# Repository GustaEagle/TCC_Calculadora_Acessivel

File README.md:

# Calculadora científica acessível (TCC)

Calculadora científica com foco em **acessibilidade** (feedback por voz e operação sem depender só da tela), executada em **Raspberry Pi 4B** com teclado físico, **UPS HAT**, painel **LCD 4,3" Waveshare** e suporte a **monitor HDMI**.

**Equipe:** Gustavo, João, Yuri  

**Repositório:** [github.com/GustaEagle/TCC_Calculadora_Acessivel](https://github.com/GustaEagle/TCC_Calculadora_Acessivel)

---

## Documentação principal

A pasta [`docs/`](docs/README.md) está organizada **por contexto** — comece pelo índice, ou vá direto ao documento:

| Documento | Descrição |
| --------- | --------- |
| [docs/README.md](docs/README.md) | **Índice da documentação** — o que existe e em que pasta |
| [docs/produto/PRD.md](docs/produto/PRD.md) | Requisitos de produto, escopo e arquitetura em alto nível (**normativo**) |
| [docs/guias/teclado-matriz.md](docs/guias/teclado-matriz.md) | **Teclado físico (matriz 6×7)**: as 38 teclas, funções com Ctrl/Shift, GPIO e diagnóstico |
| [docs/guias/comandos-teclado.md](docs/guias/comandos-teclado.md) | Comandos no teclado de PC: Ctrl/Shift, histórico, última resposta |
| [docs/guias/build-img-linux.md](docs/guias/build-img-linux.md) | Arranque em modo kiosk no Raspberry Pi 4B |
| [docs/desenvolvimento/Sprints.md](docs/desenvolvimento/Sprints.md) | Backlog por sprint e estado das tasks |
| [docs/desenvolvimento/GITHUB_WORKFLOW.md](docs/desenvolvimento/GITHUB_WORKFLOW.md) | Fluxo Git/GitHub da equipe |
| [docs/desenvolvimento/REPO_STRUCTURE.md](docs/desenvolvimento/REPO_STRUCTURE.md) | Mapa de pastas (software, hardware, system) |
| [docs/desenvolvimento/CONTEXT.md](docs/desenvolvimento/CONTEXT.md) | Memória curta entre sessões |
| [cronograma/cronograma.md](cronograma/cronograma.md) | Linha do tempo académica |

---

## Executar

```bash
python -m pip install -r software/requirements.txt
python software/app.py
```

`software/app.py` deteta a saída de vídeo ativa e abre **um** front (PRD §7): monitor HDMI externo quando reconhecido, senão o LCD 4,3", e **modo somente áudio** quando não há vídeo utilizável.

Para desenvolvimento e demonstrações a saída pode ser forçada:

```bash
python software/app.py --force-mode hdmi   # front do monitor externo
python software/app.py --force-mode lcd    # front do painel 4,3"
python software/app.py --force-mode audio  # somente voz, sem janela
```

**Histórico:** abre por **Ctrl + Ans** (no PC, a tecla `a` faz o papel do `Ans` da matriz 6x7). Não há botão de histórico — a entrada é sempre pelo teclado.

Lista completa dos atalhos: [docs/guias/teclado-matriz.md](docs/guias/teclado-matriz.md) (teclado do produto) e [docs/guias/comandos-teclado.md](docs/guias/comandos-teclado.md) (teclado de PC).

Testes: `make check` (ou `python -m unittest discover -s software/tests -t .`).

---

## Estrutura do repositório (resumo)

- **`software/`** — Motor de cálculo, UI (LCD / HDMI / partilhada), acessibilidade (áudio/TTS), plataforma (GPIO, integração), ponto de entrada `app.py`
- **`hardware/`** — PCB (KiCad), snapshots de export para marcos
- **`system/`** — Imagem SO, arranque e scripts (evolução conforme o PRD)
- **`docs/`** — Documentação por contexto: `produto/` (PRD), `guias/` (uso e montagem), `desenvolvimento/` (processo), `testes/`, mais referência de hardware (`raspberry-pi-4b/`, `waveshare/`, `keyboard-layout/`, `cad/`)
- **`cronograma/`** — Cronograma em Markdown, HTML interativo e export bruto
- **`prompts/`** — Prompts de sessão (bootstrap, fecho, agentes)

---

## Contribuir

1. Clonar o repositório e entrar na pasta do projeto  
2. Ler [docs/desenvolvimento/GITHUB_WORKFLOW.md](docs/desenvolvimento/GITHUB_WORKFLOW.md) e, no início de cada sessão, seguir [prompts/bootstrap.txt](prompts/bootstrap.txt)  
3. Trabalhar em branch a partir de `main` atualizada; mensagens de commit em **inglês** (ver [.github/COMMIT_GUIDELINES.md](.github/COMMIT_GUIDELINES.md))

---

## Estado do projeto

O código de aplicação ainda está em estruturação; o PRD e a documentação de apoio são a referência normativa. Consulte [docs/desenvolvimento/Sprints.md](docs/desenvolvimento/Sprints.md) para a sprint corrente e próximos entregáveis.

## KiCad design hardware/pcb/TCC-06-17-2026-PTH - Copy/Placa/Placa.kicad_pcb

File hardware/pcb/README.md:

# PCB — KiCad

Coloque aqui o **projeto principal** (ex.: `tcc-calculadora/` com `.kicad_pro`).

## Snapshots (marcos)

Exportações conscientes (não substituem o Git do projeto):

```
snapshots/
  2026-05-01-pre-banca/
  2026-06-10-entrega/
```

Cada pasta pode conter: Gerber ZIP, PDF do esquemático, lista de materiais, notas de revisão.

## O que não versionar

A pasta **`.history/`** gerada pelo KiCad fica fora do Git (ver `.gitignore` na raiz).

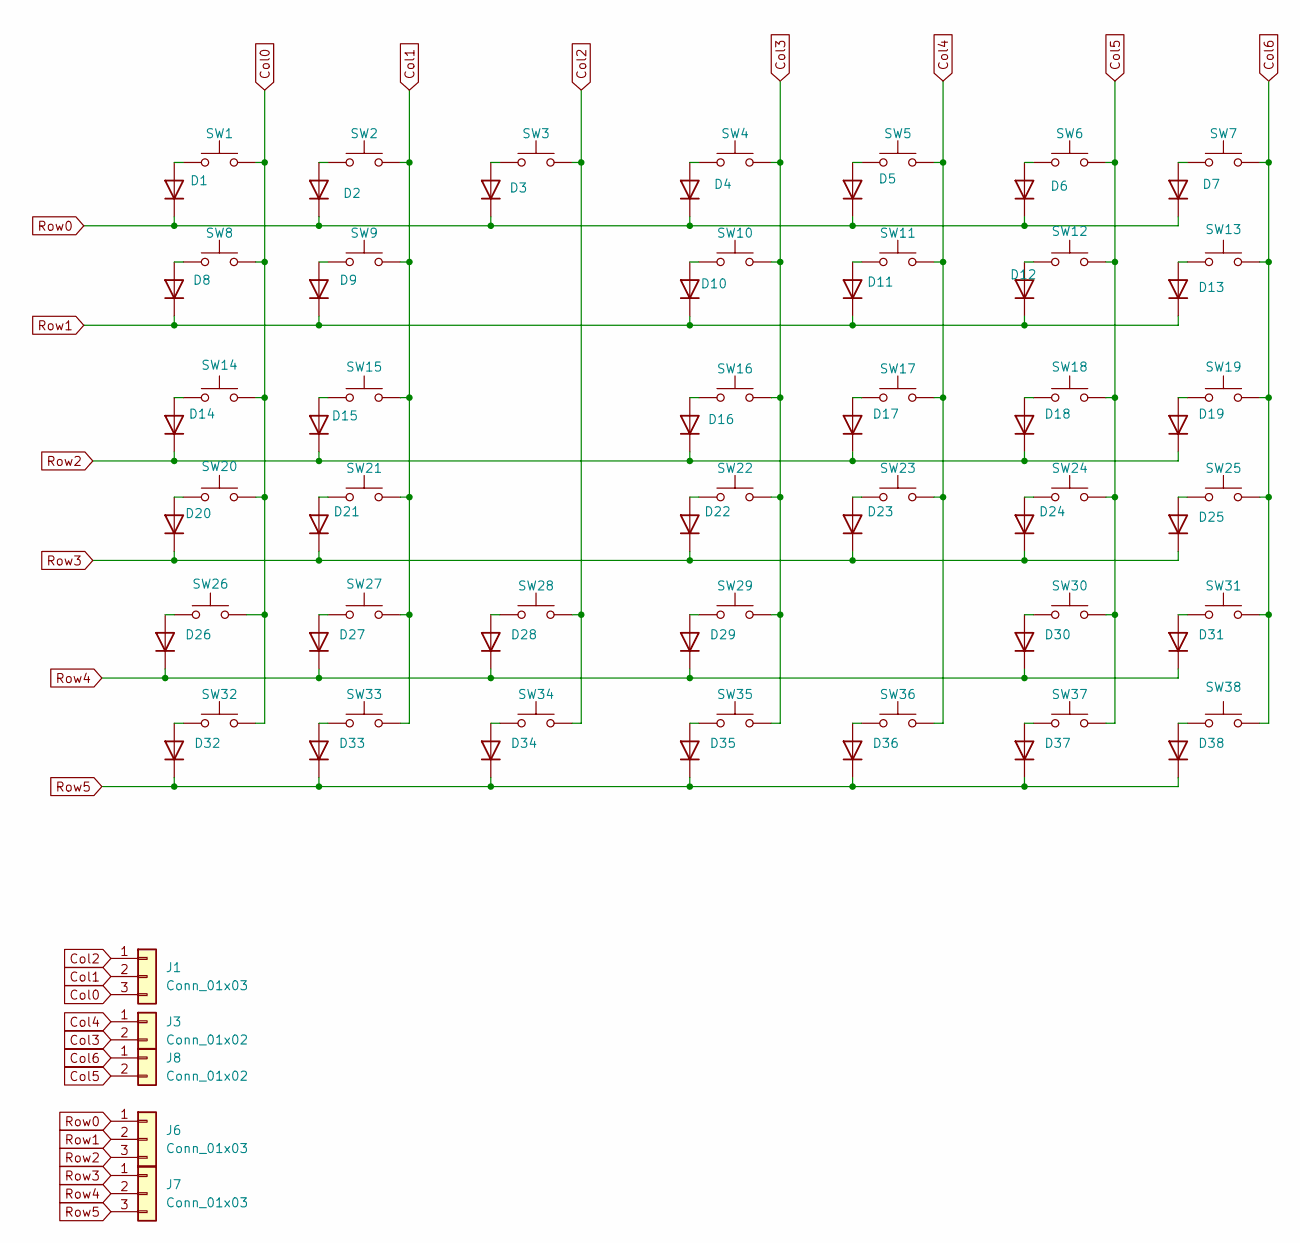
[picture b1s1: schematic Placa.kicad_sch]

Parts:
D1, D2, D3, D4, D5, D6, D7, D8, D9, D10, D11, D12, D13, D14, D15, D16, D17, D18, D19, D20, D21, D22, D23, D24, D25, D26, D27, D28, D29, D30, D31, D32, D33, D34, D35, D36, D37, D38: 1N4148; D_DO-35_SOD27_P7.62mm_Horizontal
J1, J6, J7: Conn_01x03; JST_XH_B3B-XH-A_1x03_P2.50mm_Vertical
J3, J8: Conn_01x02; JST_XH_B2B-XH-A_1x02_P2.50mm_Vertical
SW1, SW2, SW3, SW4, SW5, SW6, SW7, SW8, SW9, SW10, SW11, SW12, SW13, SW14, SW15, SW16, SW17, SW18, SW19, SW20, SW21, SW22, SW23, SW24, SW25, SW26, SW27, SW28, SW29, SW30, SW31, SW32, SW33, SW34, SW35, SW36, SW37, SW38: SW_Push; Kailh_socket_MX_platemount

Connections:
Col0: J1.3, SW1.2, SW8.2, SW14.2, SW20.2, SW26.2, SW32.2
Col1: J1.2, SW2.2, SW9.2, SW15.2, SW21.2, SW27.2, SW33.2
Col2: J1.1, SW3.2, SW28.2, SW34.2
Col3: J3.2, SW4.2, SW10.2, SW16.2, SW22.2, SW29.2, SW35.2
Col4: J3.1, SW5.2, SW11.2, SW17.2, SW23.2, SW36.2
Col5: J8.2, SW6.2, SW12.2, SW18.2, SW24.2, SW30.2, SW37.2
Col6: J8.1, SW7.2, SW13.2, SW19.2, SW25.2, SW31.2, SW38.2
unnamed: D1.2 (A), SW1.1
unnamed: D2.2 (A), SW2.1
unnamed: D3.2 (A), SW3.1
unnamed: D4.2 (A), SW4.1
unnamed: D5.2 (A), SW5.1
unnamed: D6.2 (A), SW6.1
unnamed: D7.2 (A), SW7.1
unnamed: D8.2 (A), SW8.1
unnamed: D9.2 (A), SW9.1
unnamed: D10.2 (A), SW10.1
unnamed: D11.2 (A), SW11.1
unnamed: D12.2 (A), SW12.1
unnamed: D13.2 (A), SW13.1
unnamed: D14.2 (A), SW14.1
unnamed: D15.2 (A), SW15.1
unnamed: D16.2 (A), SW16.1
unnamed: D17.2 (A), SW17.1
unnamed: D18.2 (A), SW18.1
unnamed: D19.2 (A), SW19.1
unnamed: D20.2 (A), SW20.1
unnamed: D21.2 (A), SW21.1
unnamed: D22.2 (A), SW22.1
unnamed: D23.2 (A), SW23.1
unnamed: D24.2 (A), SW24.1
unnamed: D25.2 (A), SW25.1
unnamed: D26.2 (A), SW26.1
unnamed: D27.2 (A), SW27.1
unnamed: D28.2 (A), SW28.1
unnamed: D29.2 (A), SW29.1
unnamed: D30.2 (A), SW30.1
unnamed: D31.2 (A), SW31.1
unnamed: D32.2 (A), SW32.1
unnamed: D33.2 (A), SW33.1
unnamed: D34.2 (A), SW34.1
unnamed: D35.2 (A), SW35.1
unnamed: D36.2 (A), SW36.1
unnamed: D37.2 (A), SW37.1
unnamed: D38.2 (A), SW38.1
Row0: D1.1 (K), D2.1 (K), D3.1 (K), D4.1 (K), D5.1 (K), D6.1 (K), D7.1 (K), J6.1
Row1: D8.1 (K), D9.1 (K), D10.1 (K), D11.1 (K), D12.1 (K), D13.1 (K), J6.2
Row2: D14.1 (K), D15.1 (K), D16.1 (K), D17.1 (K), D18.1 (K), D19.1 (K), J6.3
Row3: D20.1 (K), D21.1 (K), D22.1 (K), D23.1 (K), D24.1 (K), D25.1 (K), J7.1
Row4: D26.1 (K), D27.1 (K), D28.1 (K), D29.1 (K), D30.1 (K), D31.1 (K), J7.2
Row5: D32.1 (K), D33.1 (K), D34.1 (K), D35.1 (K), D36.1 (K), D37.1 (K), D38.1 (K), J7.3

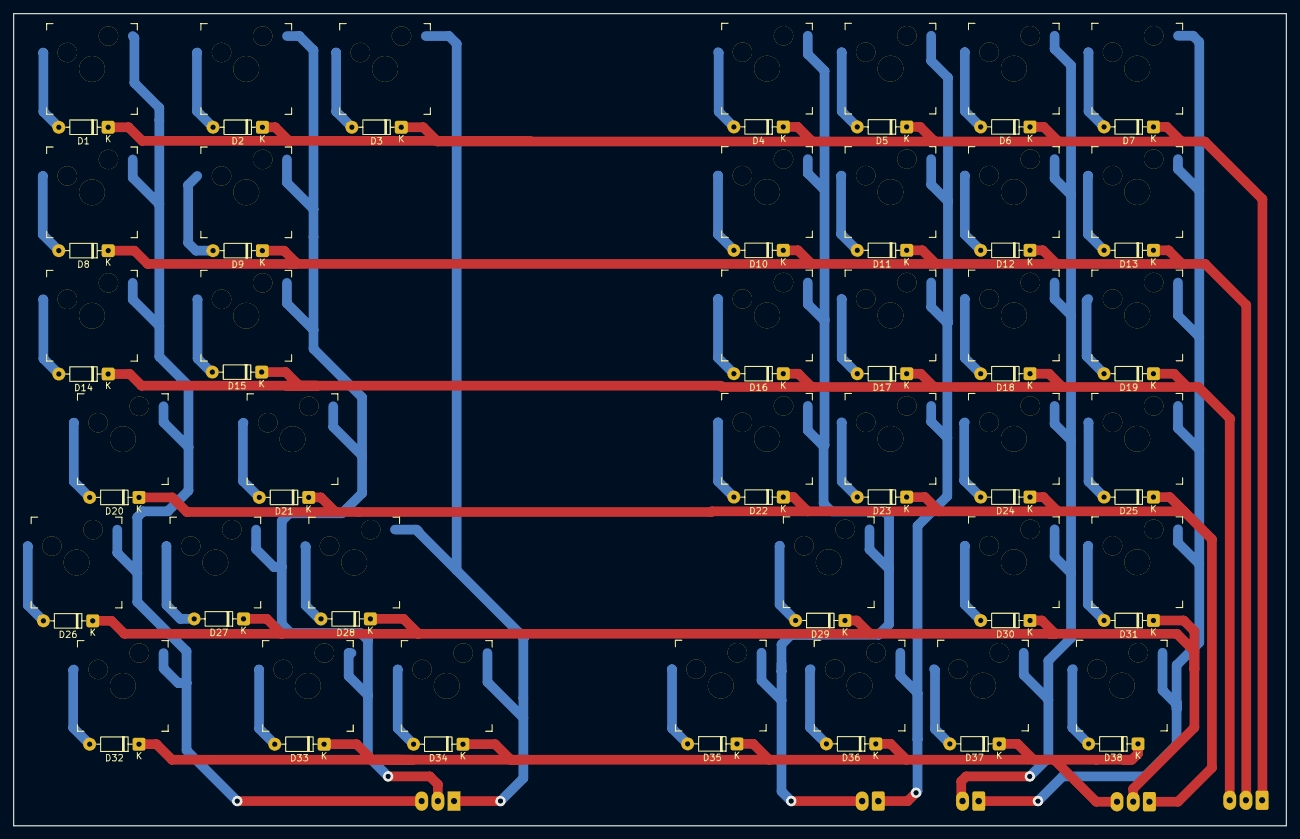
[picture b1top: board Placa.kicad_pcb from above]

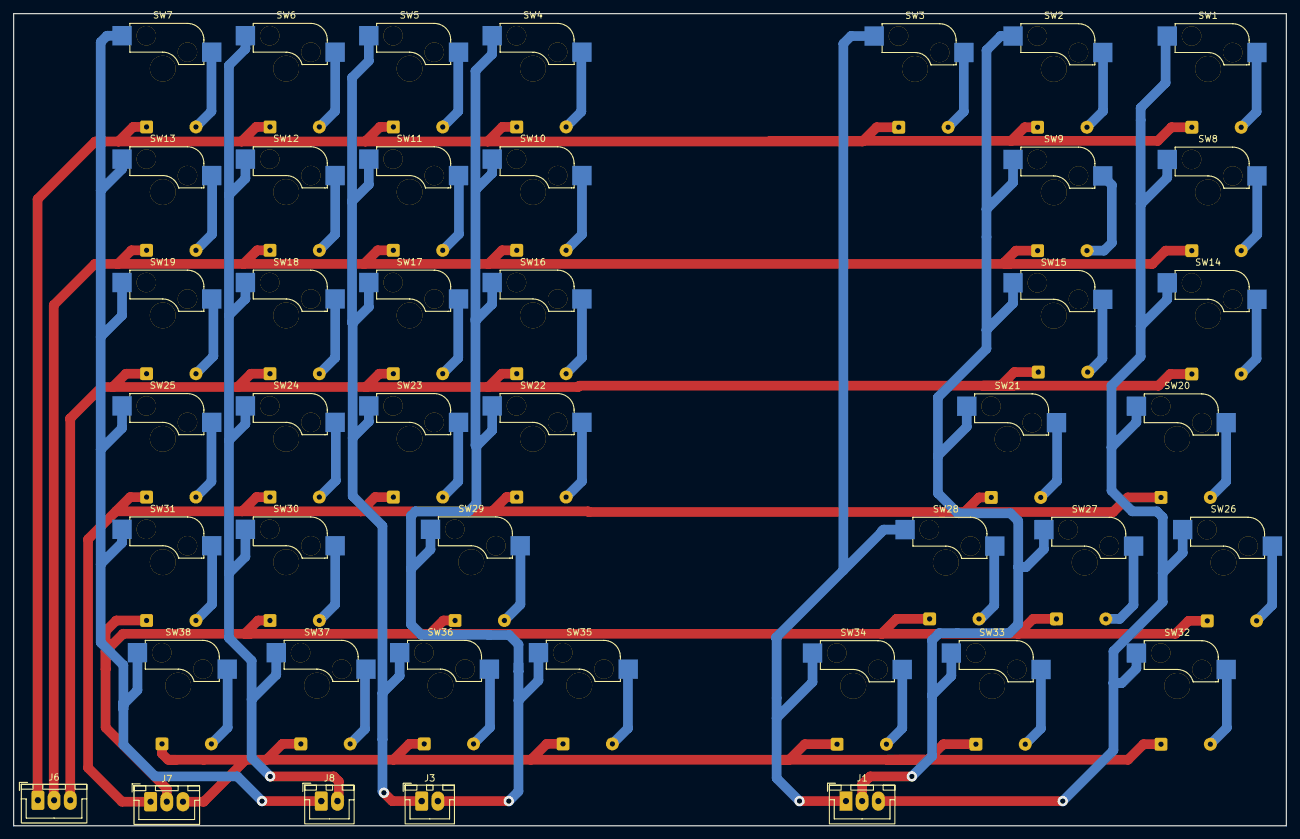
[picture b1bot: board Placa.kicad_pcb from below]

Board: 2 copper layers, 196.5 x 125.4 mm, 81 parts (5 on the bottom side), 51 nets.

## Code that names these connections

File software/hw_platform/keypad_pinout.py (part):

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
# Linhas: L0..L2 nos pinos do SPI0 (19/21/23) e L3..L5 em ímpares contíguos
# (11/13/15). Ordem conferida eletricamente na bancada: uma versão anterior
# desta tabela tinha Row0<->Row2 e Row3<->Row5 trocadas (mesmos GPIOs, ordem
# errada), o que nenhum teste de conjunto apanhava. L3..L5 já estiveram em
# GPIO4/3/2 (pinos 7/5/3) e foram movidas: GPIO2/GPIO3 são o I2C1, o
# barramento que o UPS HAT precisa (0x42, RF-06/RF-14), e têm pull-ups de
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
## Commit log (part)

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2026-04-18 Initial import: PRD, docs, cronograma, hardware skeleton, and team workflow
    Made-with: Cursor
2026-04-18 docs: update CONTEXT after initial GitHub push
    Made-with: Cursor
2026-04-18 docs: expand README with project overview and doc links
    Made-with: Cursor
2026-04-18 Remove contribution section from README
    Removed contribution guidelines and related instructions from the README.
2026-04-18 docs: add TCC written part (Calculadora rev04.docx) and link in README
    Made-with: Cursor
2026-04-18 docs: restore README sections after merge (Contribuir, spacing)
    Made-with: Cursor
2026-04-18 docs: create materials and methods document and update sprint context
2026-04-18 docs: update weekly records for session close
2026-04-20 Add index.html in root
2026-04-20 test pages
2026-04-28 update pcb artifacts and refresh project scaffolding/docs
    Includes latest KiCad board/project changes, generated PCB PDF exports, and repository housekeeping updates across docs and software/hardware placeholder structure.
    Made-with: Cursor
2026-05-09 hardware(pcb): refresh KiCad project and move snapshot to TCC-09-05-2026
2026-05-09 feat(ui): add ttkbootstrap calculator prototype and Python core
2026-05-10 feat: implement CTRL support, audio feedback, and requirements validation
2026-05-10 refactor: update application layout
2026-05-10 hotfix: fix calculation errors and calculator functionality issues
2026-05-11 feature/alteracoes-furos-footprint
2026-05-12 fix(pcb): correct component footprints and drill sizes
2026-05-14 chore: minor tweaks and bug fixes
2026-05-16 feat: add logBase function
2026-05-17 feat: ajusta motor de cálculo e adiciona log baseado em variável
2026-05-17 fix: improve calculation engine precision and scientific operations
2026-06-10 fix: Ajuste no codigo responsavel por apagar funções
2026-06-10 fix/feat: corrige exclusão de funções e implementa leitura acessível das funções
2026-06-10 fix: Ajustes finais
